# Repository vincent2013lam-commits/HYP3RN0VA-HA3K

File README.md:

Heyo! PR0J3CT: #H9P3RN0VA is a musical keyboard where you can create your own custom musical tracks. H9P3RN0VA will be a PCB design, first the design process will be on a schematic editor, then transferred to the PCB editor where the music magic happens.

To make a MIDI KEYBOARD like H9P3RN0VA, open the schematic editor on Kicad and add the following components below:
- Waveshare Microcontroller: Brain of the system
- Conn 01x09 Capacitive Touch Keys: Literally the keys you play on your keyboard
- SW_PUSH Low-Profile Switches: Functions the sound when a key is pressed
- Rotary Encoder: Ensures the sound is smooth
- Bourns Slide Potentiometer: Controls the volume
- SK6812MINI-E Neopixels: Controls the lighting of the instrument

After making the scenes, we move on to assigning the footprints, the base layer to the function of our musical keyboard

We'll transfer our schematic into the PCB editor, it should look something like this:

After the inital design, we're customizing the capacitive keys footprint, transfering them to assign on the schematic, and placing them into the PCB editor:

Then, comes the wiring, edging, and rounding the corners with the Edge.cuts, F.cu, B.cu, F.silkscreen and B.silkscreen:

The 3D modeling's next, cuz what's a keyboard without 3D stuff to press and play on???

After is the fabrication, which after installing and going onto a PCB website, it will turn out like this:

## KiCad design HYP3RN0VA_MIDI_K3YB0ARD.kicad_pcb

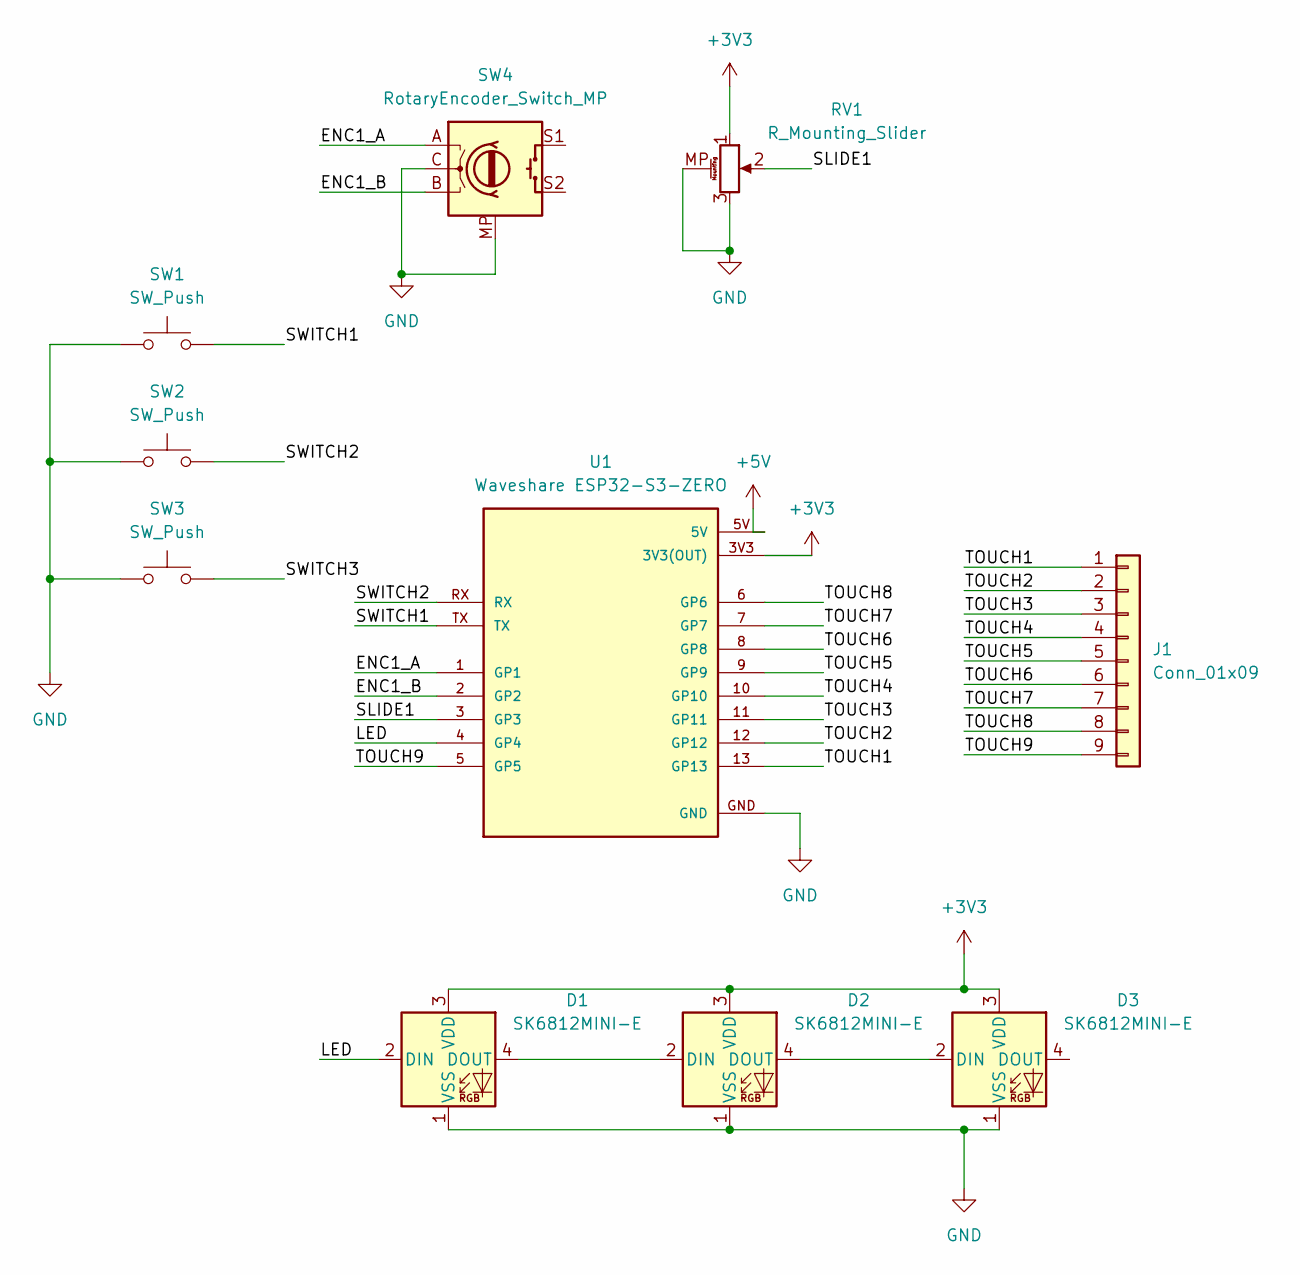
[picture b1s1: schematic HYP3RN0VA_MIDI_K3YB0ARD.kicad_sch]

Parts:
D1, D2, D3: SK6812MINI-E; LED_SK6812MINI-E_3.2x2.8mm_P1.5mm_ReverseMount
J1: Conn_01x09; Capacitive Keys
RV1: R_Mounting_Slider; Potentiometer_Bourns_PTA1543_Single_Slide
SW1, SW2, SW3: SW_Push; Kailh Choc Low-Profile Switches
SW4: RotaryEncoder_Switch_MP; RotaryEncoder_Alps_EC11E-Switch_Vertical_H20mm
U1: Waveshare ESP32-S3-ZERO; Waveshare ESP32-S3-Zero; PARTREV NA

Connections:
+3V3: D1.3 (VDD), D2.3 (VDD), D3.3 (VDD), RV1.1, U1.3V3 (3V3(OUT))
+5V: U1.5V
/ENC1_A: SW4.A, U1.1 (GP1)
/ENC1_B: SW4.B, U1.2 (GP2)
/LED: D1.2 (DIN), U1.4 (GP4)
/SLIDE1: RV1.2, U1.3 (GP3)
/SWITCH1: SW1.2, U1.TX
/SWITCH2: SW2.2, U1.RX
/SWITCH3: SW3.2
/TOUCH1: J1.1, U1.13 (GP13)
/TOUCH2: J1.2, U1.12 (GP12)
/TOUCH3: J1.3, U1.11 (GP11)
/TOUCH4: J1.4, U1.10 (GP10)
/TOUCH5: J1.5, U1.9 (GP9)
/TOUCH6: J1.6, U1.8 (GP8)
/TOUCH7: J1.7, U1.7 (GP7)
/TOUCH8: J1.8, U1.6 (GP6)
/TOUCH9: J1.9, U1.5 (GP5)
GND: D1.1 (VSS), D2.1 (VSS), D3.1 (VSS), RV1.3, RV1.MP (MountPin), SW1.1, SW2.1, SW3.1, SW4.C, SW4.MP, U1.GND
unnamed: D1.4 (DOUT), D2.2 (DIN)
unnamed: D2.4 (DOUT), D3.2 (DIN)

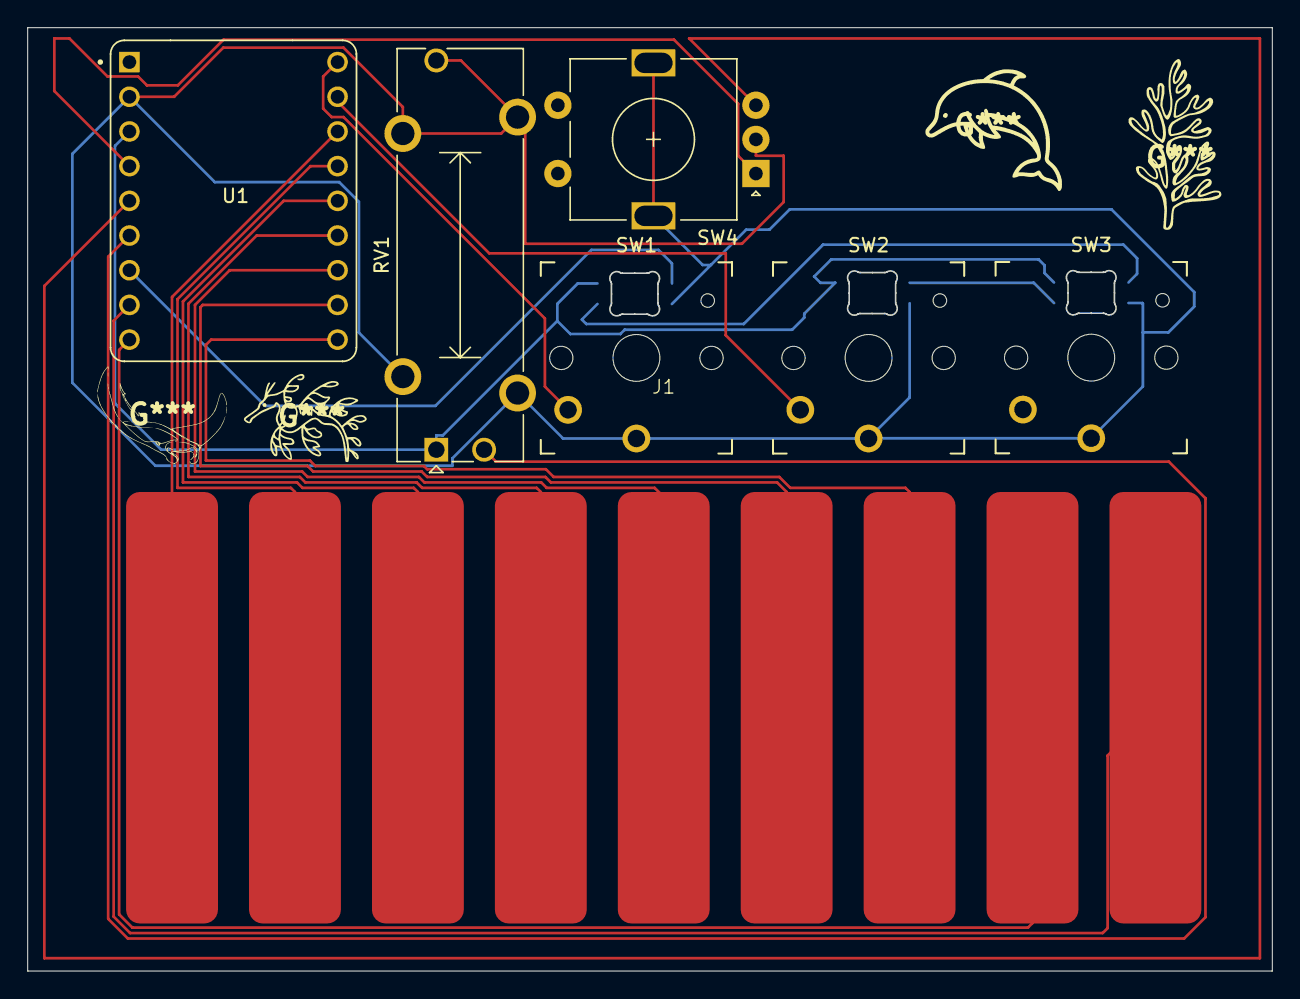
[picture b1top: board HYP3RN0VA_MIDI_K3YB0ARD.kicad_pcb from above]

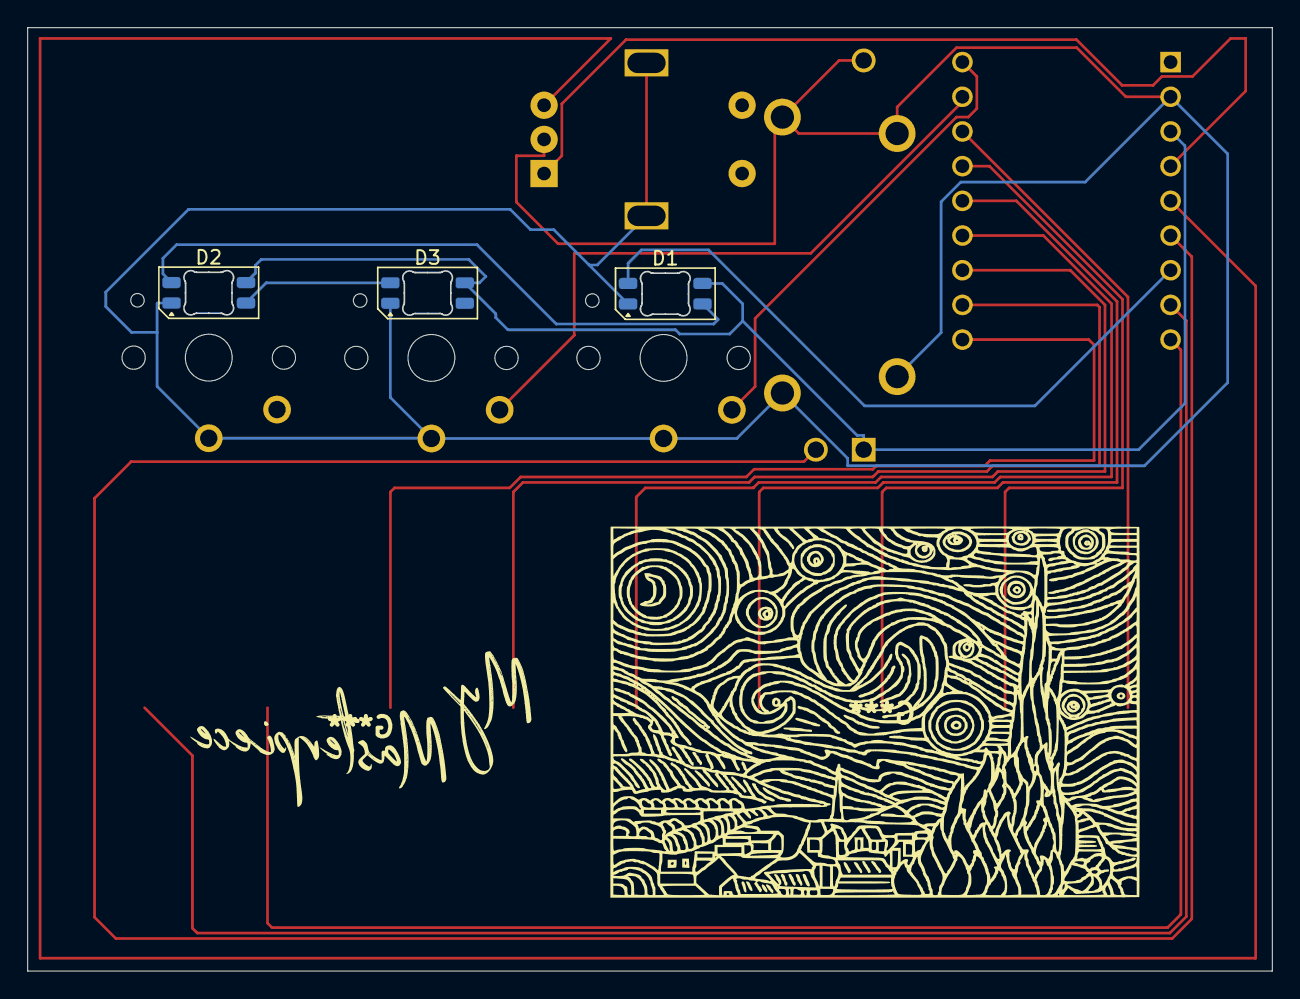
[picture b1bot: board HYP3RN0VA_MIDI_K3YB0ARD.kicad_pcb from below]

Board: 2 copper layers, 91.1 x 69.1 mm, 10 parts (3 on the bottom side), 19 nets.
